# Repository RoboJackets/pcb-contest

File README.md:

# PCB-Contest

## Overview
This is the GitHub repository for the RoboJackets Winter 2020 PCB Competition and the template for individual or team entries into the competition. This repository will also serve to serve as the place for any rules clarifications via the [FAQ](CONTEST.md#faq).

## Rules and Submission
**Please be sure to review the rules in [CONTEST.md](CONTEST.md)!**
To participate, click the green **Use this template** button. Then give your repository a name and make it **public**. You are now ready to start working! Your submission link will be a link to this new repository you made.

## Example
We have provided an example project in the [Example](Example) folder showing a submission with all required parts for this contest. Feel free to use it as a template for the BOM and Documentation as a baseline.

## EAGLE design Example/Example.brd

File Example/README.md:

# 555 Timer Motor Driver

## Overview

This is a simple board to spin an external motor using a 555 timer while being  cheap ($19.94 per the [BOM](BOM.csv)). The board is designed to be manufactured using **JLCPCB** and is a regular 2 layer board with black soldermask and an ENIG finish for aesthetics.

## Power Input

It features input power switching between 5V USB and 9V barrel jack input using the main power switch.

## 555 Timer

The direction and rotation speed are controlled using a externally wired trimpot. The rotation frequency and duty cycle for the max and min posistion of the trimpot were calculated.

## Motor

The motor is low side switched using a standard N-Channel MOSFET.

## Firmware

This board does not have any programmable components so no firmware is required.

## Images

Schematic:

Board:

3D Render:

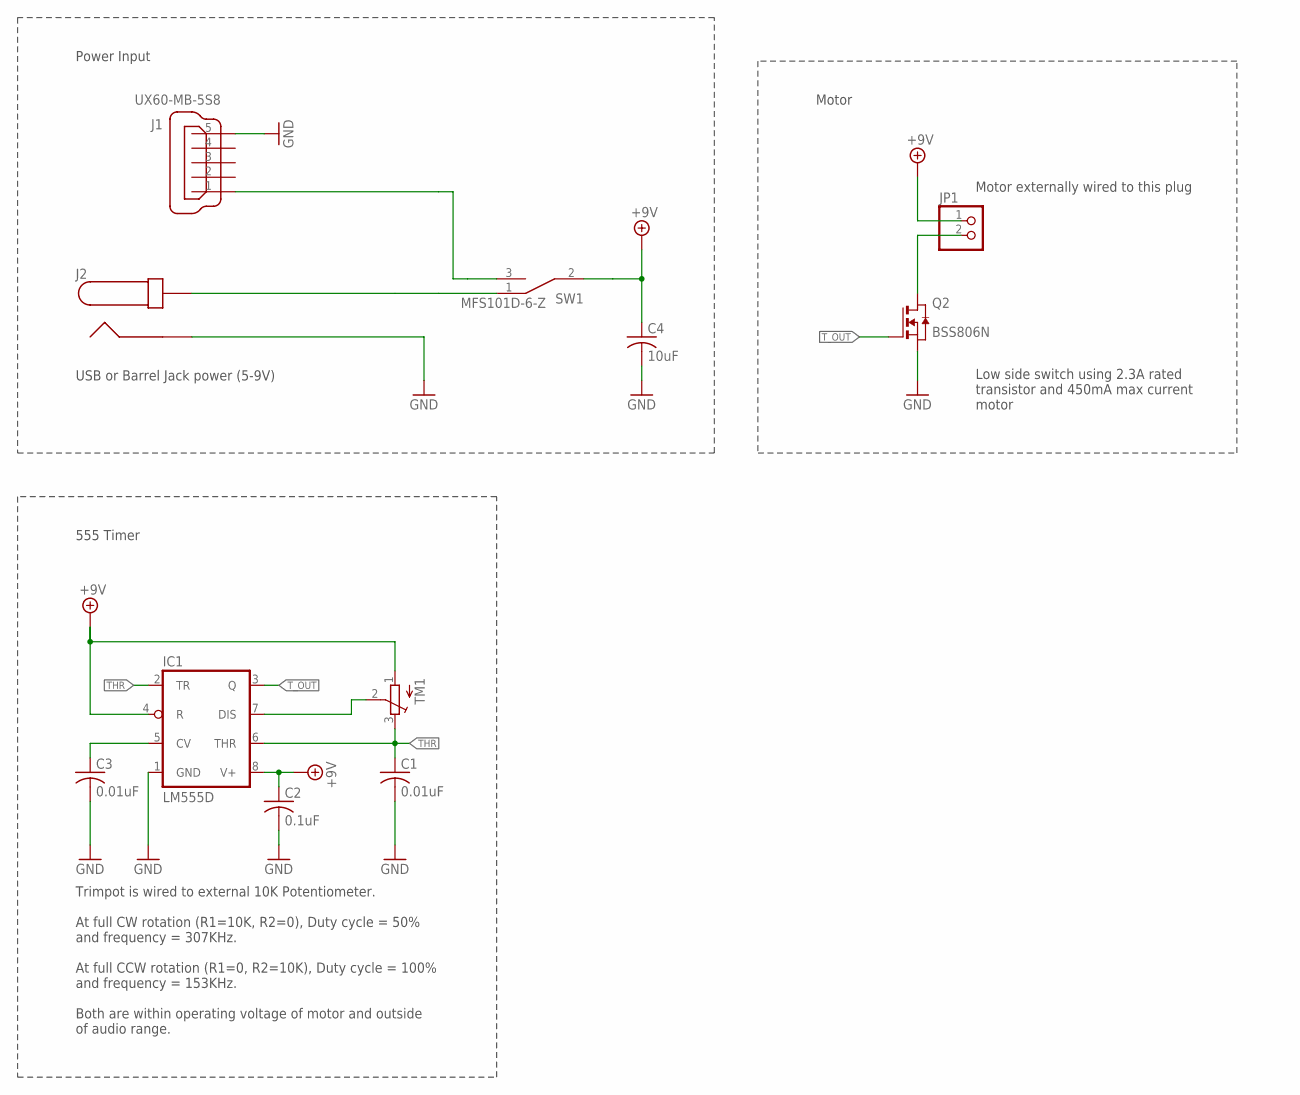
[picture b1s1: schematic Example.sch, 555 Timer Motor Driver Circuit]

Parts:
C1, C3: 0.01uF; C0603
C2: 0.1uF; C0603
C4: 10uF; C0603
IC1: LM555D; SO08
J1: UX60-MB-5S8
J2: PJ-037A
JP1: PINHD-1X2; 1X02
Q2: BSS806N; SOT-23-3
SW1: MFS101D-6-Z
TM1: TRIMPOT3386; TRIM-3386

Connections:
+9V: C2.1, C4.1, IC1.4 (R), IC1.8 (V+), JP1.1, SW1.2 (COMMON), TM1.1 (A)
GND: C1.2, C2.2, C3.2, C4.2, IC1.1 (GND), J1.5, J2.P$1 (2), Q2.2 (S)
unnamed: IC1.7 (DIS), TM1.2 (S)
unnamed: JP1.2, Q2.3 (D)
unnamed: C3.1, IC1.5 (CV)
unnamed: J1.1, SW1.3 (B)
unnamed: J2.P$2 (1), SW1.1 (A)
THR: C1.1, IC1.2 (TR), IC1.6 (THR), TM1.3 (E)
T_OUT: IC1.3 (Q), Q2.1 (G)

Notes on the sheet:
Trimpot is wired to external 10K Potentiometer. At full CW rotation (R1=10K, R2=0), Duty cycle = 50% and frequency = 307KHz. At full CCW rotation (R1=0, R2=10K), Duty cycle = 100% and frequency = 153KHz. Both are within operating voltage of motor and outside of audio range.
Motor externally wired to this plug
Low side switch using 2.3A rated transistor and 450mA max current motor
USB or Barrel Jack power (5-9V)
Power Input
555 Timer
Motor

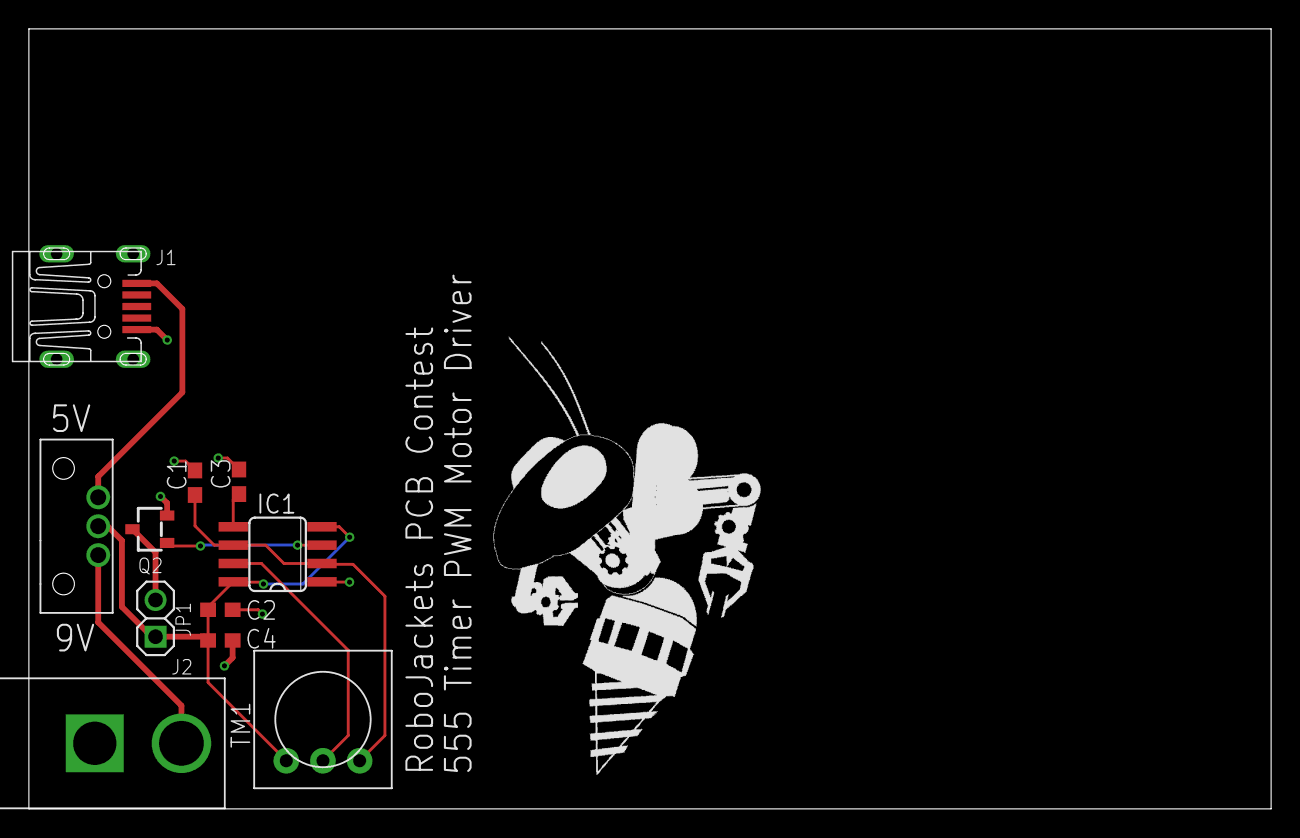
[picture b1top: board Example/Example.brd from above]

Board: 2 copper layers, 86.0 x 54.0 mm, 12 parts (0 on the bottom side), 9 nets.

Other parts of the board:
U$2: ROBOBUZZ_1.4X

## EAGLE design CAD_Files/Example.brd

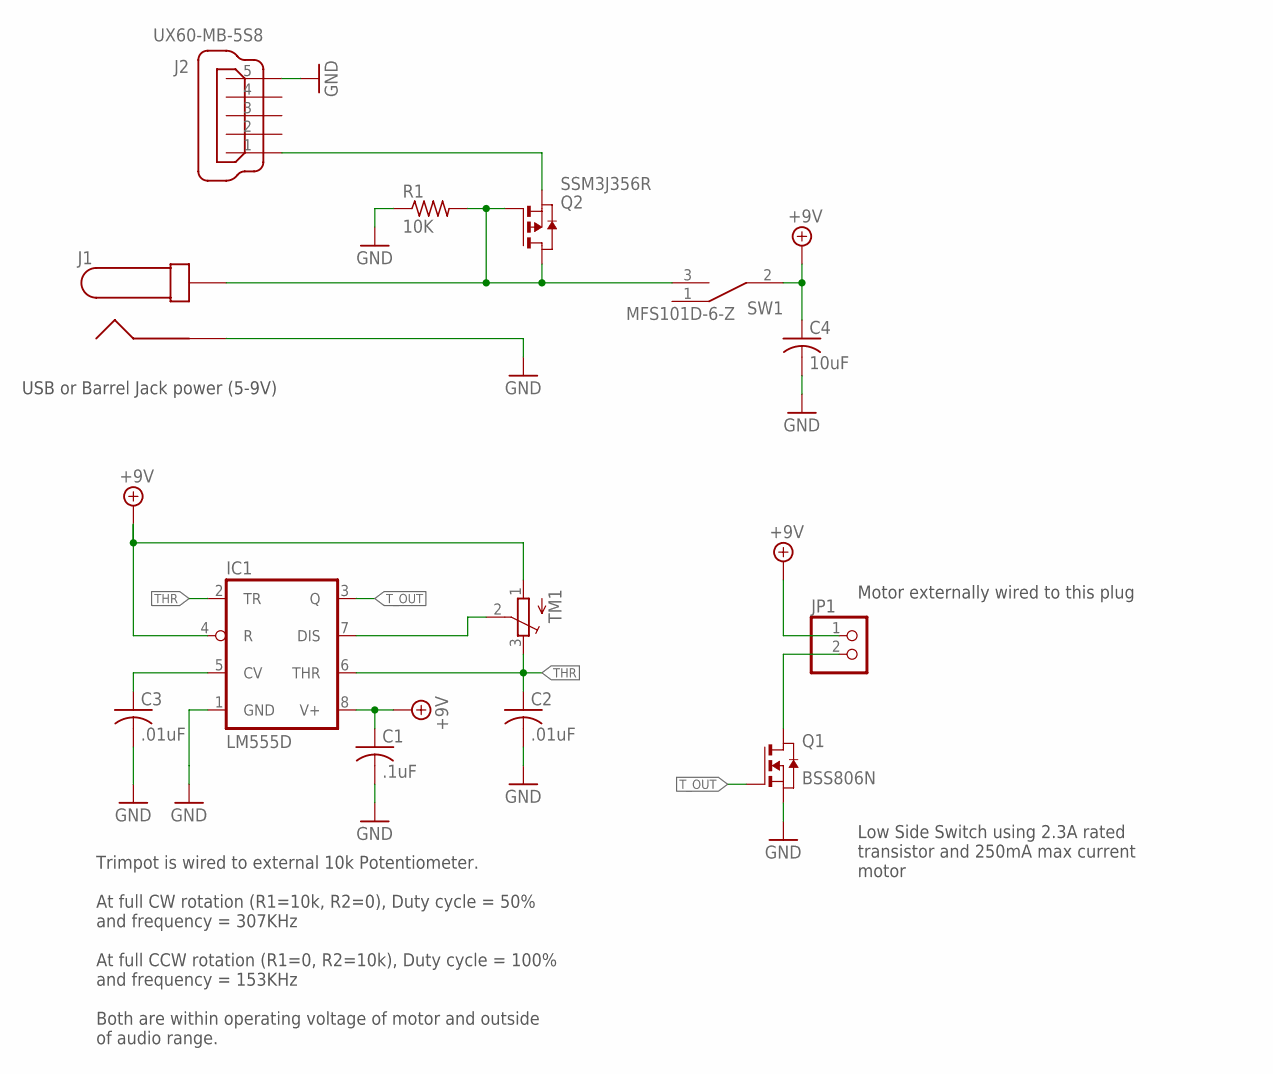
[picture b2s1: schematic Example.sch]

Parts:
C1: .1uF; C0603
C2, C3: .01uF; C0603
C4: 10uF; C0603
IC1: LM555D; SO08
J1: PJ-037A
J2: UX60-MB-5S8
JP1: PINHD-1X2; 1X02
Q1: BSS806N; SOT-23-3
Q2: SSM3J356R; SOT95P240X80-3N
R1: 10K; R0603
SW1: MFS101D-6-Z
TM1: TRIMPOT3386; TRIM-3386

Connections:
+9V: C1.1, C4.1, IC1.4 (R), IC1.8 (V+), JP1.1, SW1.2 (COMMON), TM1.1 (A)
GND: C1.2, C2.2, C3.2, C4.2, IC1.1 (GND), J1.P$1 (2), J2.5, Q1.2 (S), R1.1
unnamed: IC1.7 (DIS), TM1.2 (S)
unnamed: JP1.2, Q1.3 (D)
unnamed: C3.1, IC1.5 (CV)
unnamed: J2.1, Q2.3 (S)
unnamed: J1.P$2 (1), Q2.1 (G), Q2.2 (D), R1.2, SW1.3 (B)
THR: C2.1, IC1.2 (TR), IC1.6 (THR), TM1.3 (E)
T_OUT: IC1.3 (Q), Q1.1 (G)

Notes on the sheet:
Trimpot is wired to external 10k Potentiometer. At full CW rotation (R1=10k, R2=0), Duty cycle = 50% and frequency = 307KHz At full CCW rotation (R1=0, R2=10k), Duty cycle = 100% and frequency = 153KHz Both are within operating voltage of motor and outside of audio range.
Motor externally wired to this plug
Low Side Switch using 2.3A rated transistor and 250mA max current motor
USB or Barrel Jack power (5-9V)

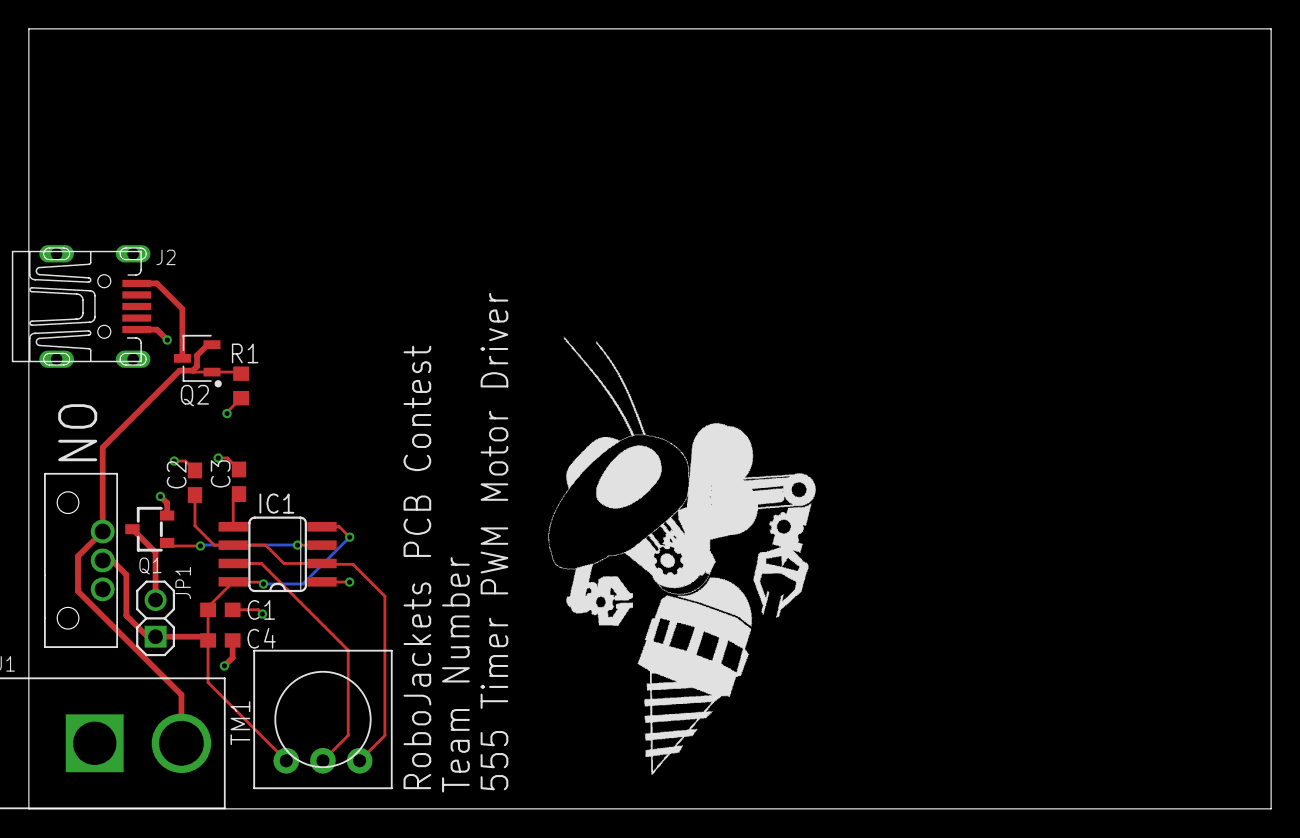
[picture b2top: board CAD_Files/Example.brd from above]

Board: 2 copper layers, 86.0 x 54.0 mm, 14 parts (0 on the bottom side), 9 nets.

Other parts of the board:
U$2: ROBOBUZZ_1.4X

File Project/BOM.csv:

Qty,Value,Device,Parts,Description,DKPN,Price
1,,PINHD-1X2,JP1,PIN HEADER,609-3507-ND, $0.12 
1,,PJ-037A,J1,Barrel Jack 2.1x5.5mm,CP-037A-ND, $0.58 
1,,TRIMPOT3386,TM1,Placeholder for externally wired 10k Pot,987-1662-ND, $0.79 
2,.01uF,C-USC0603,"C2, C3","CAPACITOR, American symbol",478-0603YD103KAT2ACT-ND, $0.10 
1,.1uF,C-USC0603,C1,"CAPACITOR, American symbol",1276-CL10B104KB8NNNLCT-ND, $0.10 
1,10K,R-US_R0603,R1,"RESISTOR, American symbol",RNCP0603FTD10K0CT-ND, $0.10 
1,10uF,C-USC0603,C4,"CAPACITOR, American symbol",1276-6769-1-ND, $0.27 
1,BSS806N,BSS806N,Q1,N-Channel MOSFET,BSS806NH6327XTSA1CT-ND, $0.46 
1,LM555D,LM555D,IC1,555 TIMER,296-6501-1-ND, $0.36 
1,MFS101D-6-Z,MFS101D-6-Z,SW1,SPDT Slide Switch,563-1555-ND, $1.09 
1,SSM3J356R,SSM3J356R,Q2,P-Channel 60V 2A (Ta) 1W (Ta) Surface Mount SOT-23F,SSM3K339RLFCT-ND, $0.43 
1,UX60-MB-5S8,UX60-MB-5S8,J2,Mini USB Port,H2960CT-ND, $0.93 
,,,,,Total:, $5.33

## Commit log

2020-11-25 Initial Commit with readme
2020-11-25 Made 555 Timer Motor Circuit, added .gitignore
2020-11-25 Removed .gitignore to put elsewhere
2020-11-25 Added .gitignore for eagle files
2020-11-25 Added picture and silkscreen
2020-11-25 Added decoupling capacitors, fixed Library style guide compliance
2020-11-25 Added DKPN
2020-11-26 Library edits, power switching transistor, 3d CAD
2020-12-05 Adjusted example to be final dimensions and fixed silkscreen
2020-12-05 Adjusted folder structure
2020-12-05 Renamed root file
2020-12-06 Edited parts
2020-12-06 Added dimensions to board
2020-12-06 Added Bill of Materials and DKPN to missing part in library
2020-12-07 rules added
2020-12-07 fixed headings
2020-12-07 fixed indents
2020-12-07 Made schematic neater
2020-12-07 edited silkscreen and re-exported renders
2020-12-07 Renamed png
2020-12-07 Cleaning up example
2020-12-07 Fixed things
2020-12-07 Wrote a thing
2020-12-07 Finished example project
2020-12-07 Adjusted README
2020-12-07 Adjusted contest rules
2020-12-07 Cleaned up formatting
2020-12-07 Updated FAQ
2020-12-07 Added git resources
2020-12-07 Added README
2020-12-07 Added FAQ link
2020-12-07 Fixed links
2020-12-07 Fixed typos
2020-12-07 Generic names
2020-12-07 Fixed typos and wordings in rules
2020-12-07 Fixed broken circuit and made new render
2020-12-07 Edited example schematic
2020-12-07 Updated BOM and README after removing part
2020-12-07 Adjusted example
2020-12-07 Fixed formatting
